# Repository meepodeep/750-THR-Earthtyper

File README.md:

# 750-THR-Earthtyper
The 1000-THR Earthmover shrunk down to a keyboard size!

# Why does this exist
I wanted to make an ultrakill themed keyboard, so i did!
# How to software
 1. DO BEFORE BUILD ITS EASIER I THINK
 2. Download QMK Toolbox and flash earthtyper via.hex onto the teensy by plugging it in, hitting the boot button and flashing. 
# How to build
1. solder the keyswitches onto the front of pcb using the laser cut Keyboard plate.svg , along with the teensy 2.0 and diodes on the back
2. Attach led strips to the inside of the case

4. Mask, engrave and cut the rear plate out of acrylic benjamin back.svg

5. Paint the engraved back plate
  
6. mount the keyboard pcb with m2 screws

7. cut the internal usb cable short on the mini b end

8. resolder the wire together so it doesnt have to coil and the usb c can still reach the outside
  
10. Use whatever method of securing the usb c cable to the pcb so that it aligns with the hole in the case

11. plug the mini b cable into the teensy.
 
12. mount the front peice with m3 screws while having the back plate on

#BOM
|Item                         |Price  |Quantity     |Use                       |Link                                                                                                                                                                                                                                                                                                                                                                                                                                                                                                                                                                                                                                      |
|-----------------------------|-------|-------------|--------------------------|------------------------------------------------------------------------------------------------------------------------------------------------------------------------------------------------------------------------------------------------------------------------------------------------------------------------------------------------------------------------------------------------------------------------------------------------------------------------------------------------------------------------------------------------------------------------------------------------------------------------------------------|
|KTT Kang White V3            |$24.89 |1x 90pcs     |Keyswitches               |https://www.aliexpress.us/item/3256807301426125.html?spm=a2g0o.detail.0.0.3d1b6S4E6S4EFs&mp=1&pdp_npi=5%40dis%21USD%21USD%2029.28%21USD%2024.89%21%21USD%2024.89%21%21%21%402101e83017622042732346918e6bca%2112000040979340369%21ct%21US%214381910819%21%211%210&gatewayAdapt=glo2usa                                                                                                                                                                                                                                                                                                                                                     |
|WS2812B 5v 2m 30 leds        |$5.16  |1x 2m 30 ip30|backlight                 |https://www.aliexpress.us/item/3256804103077154.html?spm=a2g0o.detail.0.0.58ecoyj9oyj91V&mp=1&pdp_npi=5%40dis%21USD%21USD%209.93%21USD%205.16%21%21USD%205.16%21%21%21%40210337c117622045728231910e80cb%2112000038338767353%21ct%21US%214381910819%21%211%210&gatewayAdapt=glo2usa                                                                                                                                                                                                                                                                                                                                                        |
|Teensy 2.0                   |$9.18  |1X           |mcu                       |https://www.aliexpress.us/item/3256803067426595.html?spm=a2g0o.tesla.0.0.4250OXmpOXmpuX&afTraceInfo=1005003253741347__pc__c_ppc_item_bridge_pc_main__xOYgwFH__1762223117433&gatewayAdapt=glo2usa4itemAdapt                                                                                                                                                                                                                                                                                                                                                                                                                                |
|usb adapter 20cm V8F-V3ST    |$2.24  |1x           |adapt the usb             |https://www.aliexpress.us/item/3256805661411472.html?spm=a2g0o.detail.0.0.79d0nuT8nuT8Ln&mp=1&pdp_npi=5%40dis%21USD%21USD%202.24%21USD%202.24%21%21USD%202.24%21%21%21%402101d97817622274198304062ed850%2112000034562878545%21ct%21US%214381910819%21%211%210&gatewayAdapt=glo2usa                                                                                                                                                                                                                                                                                                                                                        |
|transparent keycaps          |$18.82 |1x           |cap keys                  |https://www.aliexpress.us/item/3256809158263730.html?spm=a2g0o.detail.0.0.7867x8u0x8u0Bq&mp=1&pdp_npi=5%40dis%21USD%21USD%2020.05%21USD%2018.82%21%21USD%2018.82%21%21%21%40210337c117622048939932539e80cb%2112000048819835707%21ct%21US%214381910819%21%211%210&gatewayAdapt=glo2usa                                                                                                                                                                                                                                                                                                                                                     |
|1/8th in acrylic sheet       |$15    |1x           |be the backplate and plate|my makerspace!                                                                                                                                                                                                                                                                                                                                                                                                                                                                                                                                                                                                                            |
|m2 screws 4mm                |$2.24  |1x           |mount the pcb             |https://www.aliexpress.us/item/3256806812715286.html?spm=a2g0o.productlist.main.18.65975acdtLSuCT&algo_pvid=13e61948-fbdd-423b-8661-dafd5a1cd556&algo_exp_id=13e61948-fbdd-423b-8661-dafd5a1cd556-17&pdp_ext_f=%7B%22order%22%3A%22971%22%2C%22eval%22%3A%221%22%2C%22fromPage%22%3A%22search%22%7D&pdp_npi=6%40dis%21USD%213.11%212.75%21%21%213.11%212.75%21%402101f11417622055544167553ef72b%2112000038996754351%21sea%21US%214381910819%21X%211%210%21n_tag%3A-29919%3Bd%3A747bdf24%3Bm03_new_user%3A-29895&curPageLogUid=lCJAop0qt41n&utparam-url=scene%3Asearch%7Cquery_from%3A%7Cx_object_id%3A1005006999030038%7C_p_origin_prod%3A|
|m3 screws                    |$0     |gottem       |gottem                    |yo tengo                                                                                                                                                                                                                                                                                                                                                                                                                                                                                                                                                                                                                                  |
|pcbs                         |$33.74 |5x           |be a pcb                  |jlcpcb                                                                                                                                                                                                                                                                                                                                                                                                                                                                                                                                                                                                                                    |
|Diodes                       |$2.38  |2x           |be diodes                 |https://www.aliexpress.us/item/3256806058794623.html?spm=a2g0o.productlist.main.2.21c47164oKn0xm&algo_pvid=cf2a58fb-98bf-4c31-b0fb-3dd53bf9cf60&algo_exp_id=cf2a58fb-98bf-4c31-b0fb-3dd53bf9cf60-1&pdp_ext_f=%7B%22order%22%3A%22933%22%2C%22eval%22%3A%221%22%2C%22fromPage%22%3A%22search%22%7D&pdp_npi=6%40dis%21USD%211.72%211.19%21%21%2112.18%218.40%21%402101eede17622272036972994e35de%2112000036448323916%21sea%21US%214381910819%21X%211%210%21n_tag%3A-29919%3Bd%3A747bdf24%3Bm03_new_user%3A-29895&curPageLogUid=29HuQ5YR0viZ&utparam-url=scene%3Asearch%7Cquery_from%3A%7Cx_object_id%3A1005006245109375%7C_p_origin_prod%3A |
|Stablizers                   |$3.49  |             |stablize keys             |https://www.aliexpress.us/item/3256803076820380.html?spm=a2g0o.detail.0.0.44025Ziz5ZizBv&mp=1&pdp_npi=5%40dis%21USD%21USD%203.49%21USD%203.49%21%21USD%203.49%21%21%21%402101f54117624545764238043ec7b2%2112000024913121824%21ct%21US%214381910819%21%211%210&gatewayAdapt=glo2usa                                                                                                                                                                                                                                                                                                                                                        |
|Total without tax or shipping|$117.14|             |                          |                                                                                                                                                                                                                                                                                                                                                                                                                                                                                                                                                                                                                                          |
|Total                        |$121.32|             |                          |                                                                                                                                                                                                                                                                                                                                                                                                                                                                                                                                                                                                                                          |

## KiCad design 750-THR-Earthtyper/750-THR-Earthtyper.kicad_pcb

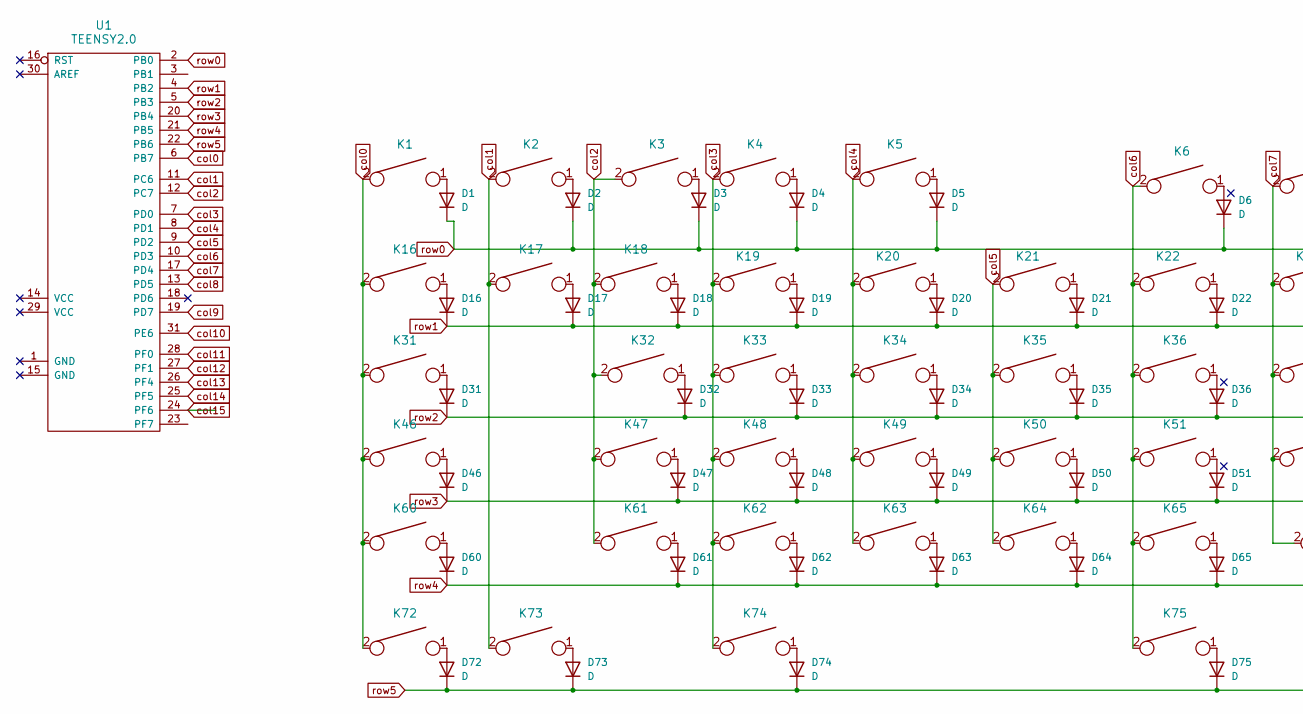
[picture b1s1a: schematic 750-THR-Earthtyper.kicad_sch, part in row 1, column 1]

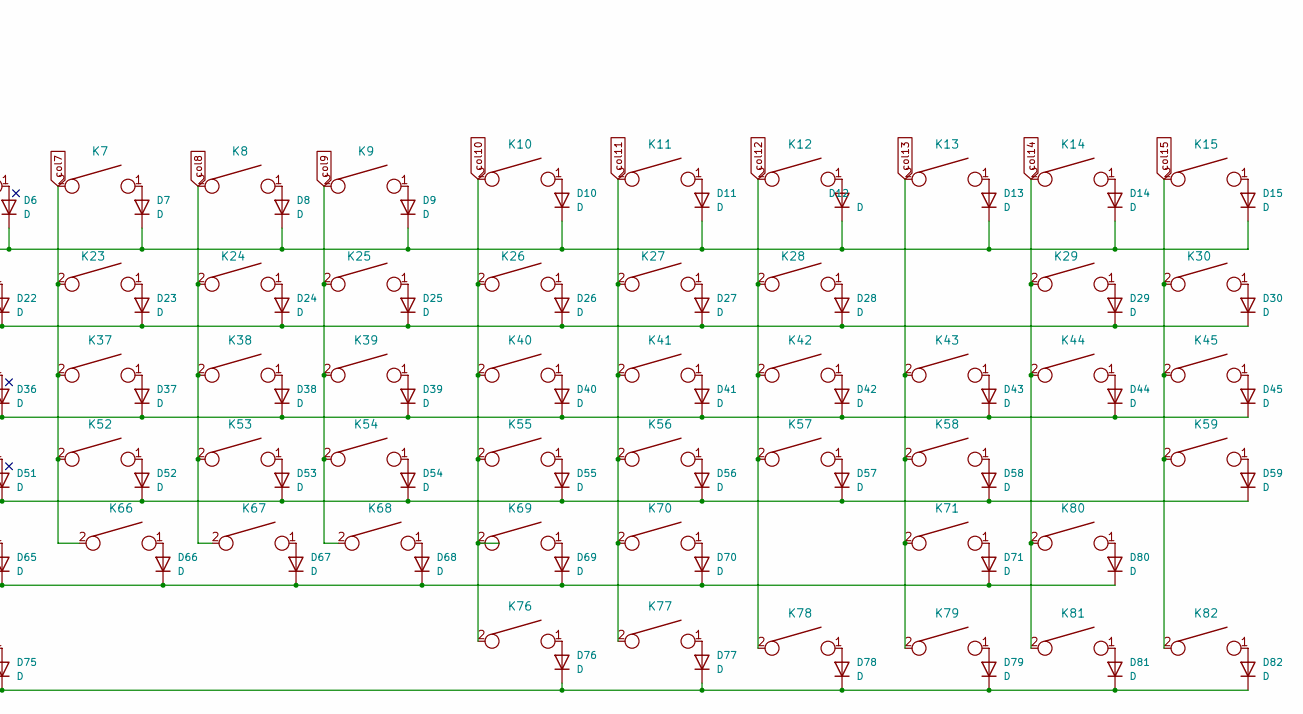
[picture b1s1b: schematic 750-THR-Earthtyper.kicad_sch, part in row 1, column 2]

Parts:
D1, D2, D3, D4, D5, D6, D7, D8, D9, D10, D11, D12, D13, D14, D15, D16, D17, D18, D19, D20, D21, D22, D23, D24, D25, D26, D27, D28, D29, D30, D31, D32, D33, D34, D35, D36, D37, D38, D39, D40, D41, D42, D43, D44, D45, D46, D47, D48, D49, D50, D51, D52, D53, D54, D55, D56, D57, D58, D59, D60, D61, D62, D63, D64, D65, D66, D67, D68, D69, D70, D71, D72, D73, D74, D75, D76, D77, D78, D79, D80, D81, D82: D; D_SOD123_axial
K1, K2, K3, K4, K5, K6, K7, K8, K9, K10, K11, K12, K13, K14, K15, K16, K17, K18, K19, K20, K21, K22, K23, K24, K25, K26, K27, K28, K30, K32, K33, K34, K35, K36, K37, K38, K39, K40, K41, K42, K43, K45, K47, K48, K49, K50, K51, K52, K53, K54, K55, K56, K57, K59, K61, K62, K63, K64, K65, K66, K67, K68, K69, K70, K71, K72, K73, K74, K75, K76, K77, K78, K79, K80, K81, K82: KEYSW; Mx_Alps_100
K29: KEYSW; Mx_Alps_200
K31, K44: KEYSW; Mx_Alps_150
K46: KEYSW; Mx_Alps_175
K58, K60: KEYSW; Mx_Alps_225
U1: TEENSY2.0; Teensy_20

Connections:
unnamed: D1.2 (A), K1.1
unnamed: D2.2 (A), K2.1
unnamed: D3.2 (A), K3.1
unnamed: D4.2 (A), K4.1
unnamed: D5.2 (A), K5.1
unnamed: D6.2 (A), K6.1
unnamed: D7.2 (A), K7.1
unnamed: D8.2 (A), K8.1
unnamed: D9.2 (A), K9.1
unnamed: D10.2 (A), K10.1
unnamed: D11.2 (A), K11.1
unnamed: D12.2 (A), K12.1
unnamed: D13.2 (A), K13.1
unnamed: D14.2 (A), K14.1
unnamed: D15.2 (A), K15.1
unnamed: D16.2 (A), K16.1
unnamed: D17.2 (A), K17.1
unnamed: D18.2 (A), K18.1
unnamed: D19.2 (A), K19.1
unnamed: D20.2 (A), K20.1
unnamed: D21.2 (A), K21.1
unnamed: D22.2 (A), K22.1
unnamed: D23.2 (A), K23.1
unnamed: D24.2 (A), K24.1
unnamed: D25.2 (A), K25.1
unnamed: D26.2 (A), K26.1
unnamed: D27.2 (A), K27.1
unnamed: D28.2 (A), K28.1
unnamed: D29.2 (A), K29.1
unnamed: D30.2 (A), K30.1
unnamed: D31.2 (A), K31.1
unnamed: D32.2 (A), K32.1
unnamed: D33.2 (A), K33.1
unnamed: D34.2 (A), K34.1
unnamed: D35.2 (A), K35.1
unnamed: D36.2 (A), K36.1
unnamed: D37.2 (A), K37.1
unnamed: D38.2 (A), K38.1
unnamed: D39.2 (A), K39.1
unnamed: D40.2 (A), K40.1
unnamed: D41.2 (A), K41.1
unnamed: D42.2 (A), K42.1
unnamed: D43.2 (A), K43.1
unnamed: D44.2 (A), K44.1
unnamed: D45.2 (A), K45.1
unnamed: D46.2 (A), K46.1
unnamed: D47.2 (A), K47.1
unnamed: D48.2 (A), K48.1
unnamed: D49.2 (A), K49.1
unnamed: D50.2 (A), K50.1
unnamed: D51.2 (A), K51.1
unnamed: D52.2 (A), K52.1
unnamed: D53.2 (A), K53.1
unnamed: D54.2 (A), K54.1
unnamed: D55.2 (A), K55.1
unnamed: D56.2 (A), K56.1
unnamed: D57.2 (A), K57.1
unnamed: D58.2 (A), K58.1
unnamed: D59.2 (A), K59.1
unnamed: D60.2 (A), K60.1
unnamed: D61.2 (A), K61.1
unnamed: D62.2 (A), K62.1
unnamed: D63.2 (A), K63.1
unnamed: D64.2 (A), K64.1
unnamed: D65.2 (A), K65.1
unnamed: D66.2 (A), K66.1
unnamed: D67.2 (A), K67.1
unnamed: D68.2 (A), K68.1
unnamed: D69.2 (A), K69.1
unnamed: D70.2 (A), K70.1
unnamed: D71.2 (A), K71.1
unnamed: D72.2 (A), K72.1
unnamed: D73.2 (A), K73.1
unnamed: D74.2 (A), K74.1
unnamed: D75.2 (A), K75.1
unnamed: D76.2 (A), K76.1
unnamed: D77.2 (A), K77.1
unnamed: D78.2 (A), K78.1
unnamed: D79.2 (A), K79.1
unnamed: D80.2 (A), K80.1
unnamed: D81.2 (A), K81.1
unnamed: D82.2 (A), K82.1
col0: K1.2, K16.2, K31.2, K46.2, K60.2, K72.2, U1.6 (PB7)
col1: K2.2, K17.2, K73.2, U1.11 (PC6)
col2: K3.2, K18.2, K32.2, K47.2, K61.2, U1.12 (PC7)
col3: K4.2, K19.2, K33.2, K48.2, K62.2, K74.2, U1.7 (PD0)
col4: K5.2, K20.2, K34.2, K49.2, K63.2, U1.8 (PD1)
col5: K21.2, K35.2, K50.2, K64.2, U1.9 (PD2)
col6: K6.2, K22.2, K36.2, K51.2, K65.2, K75.2, U1.10 (PD3)
col7: K7.2, K23.2, K37.2, K52.2, K66.2, U1.17 (PD4)
col8: K8.2, K24.2, K38.2, K53.2, K67.2, U1.13 (PD5)
col9: K9.2, K25.2, K39.2, K54.2, K68.2, U1.19 (PD7)
col10: K10.2, K26.2, K40.2, K55.2, K69.2, K76.2, U1.31 (PE6)
col11: K11.2, K27.2, K41.2, K56.2, K70.2, K77.2, U1.28 (PF0)
col12: K12.2, K28.2, K42.2, K57.2, K78.2, U1.27 (PF1)
col13: K13.2, K43.2, K58.2, K71.2, K79.2, U1.26 (PF4)
col14: K14.2, K29.2, K44.2, K80.2, K81.2, U1.25 (PF5)
col15: K15.2, K30.2, K45.2, K59.2, K82.2, U1.24 (PF6)
row0: D1.1 (K), D2.1 (K), D3.1 (K), D4.1 (K), D5.1 (K), D6.1 (K), D7.1 (K), D8.1 (K), D9.1 (K), D10.1 (K), D11.1 (K), D12.1 (K), D13.1 (K), D14.1 (K), D15.1 (K), U1.2 (PB0)
row1: D16.1 (K), D17.1 (K), D18.1 (K), D19.1 (K), D20.1 (K), D21.1 (K), D22.1 (K), D23.1 (K), D24.1 (K), D25.1 (K), D26.1 (K), D27.1 (K), D28.1 (K), D29.1 (K), D30.1 (K), U1.4 (PB2)
row2: D31.1 (K), D32.1 (K), D33.1 (K), D34.1 (K), D35.1 (K), D36.1 (K), D37.1 (K), D38.1 (K), D39.1 (K), D40.1 (K), D41.1 (K), D42.1 (K), D43.1 (K), D44.1 (K), D45.1 (K), U1.5 (PB3)
row3: D46.1 (K), D47.1 (K), D48.1 (K), D49.1 (K), D50.1 (K), D51.1 (K), D52.1 (K), D53.1 (K), D54.1 (K), D55.1 (K), D56.1 (K), D57.1 (K), D58.1 (K), D59.1 (K), U1.20 (PB4)
row4: D60.1 (K), D61.1 (K), D62.1 (K), D63.1 (K), D64.1 (K), D65.1 (K), D66.1 (K), D67.1 (K), D68.1 (K), D69.1 (K), D70.1 (K), D71.1 (K), D80.1 (K), U1.21 (PB5)
row5: D72.1 (K), D73.1 (K), D74.1 (K), D75.1 (K), D76.1 (K), D77.1 (K), D78.1 (K), D79.1 (K), D81.1 (K), D82.1 (K), U1.22 (PB6)

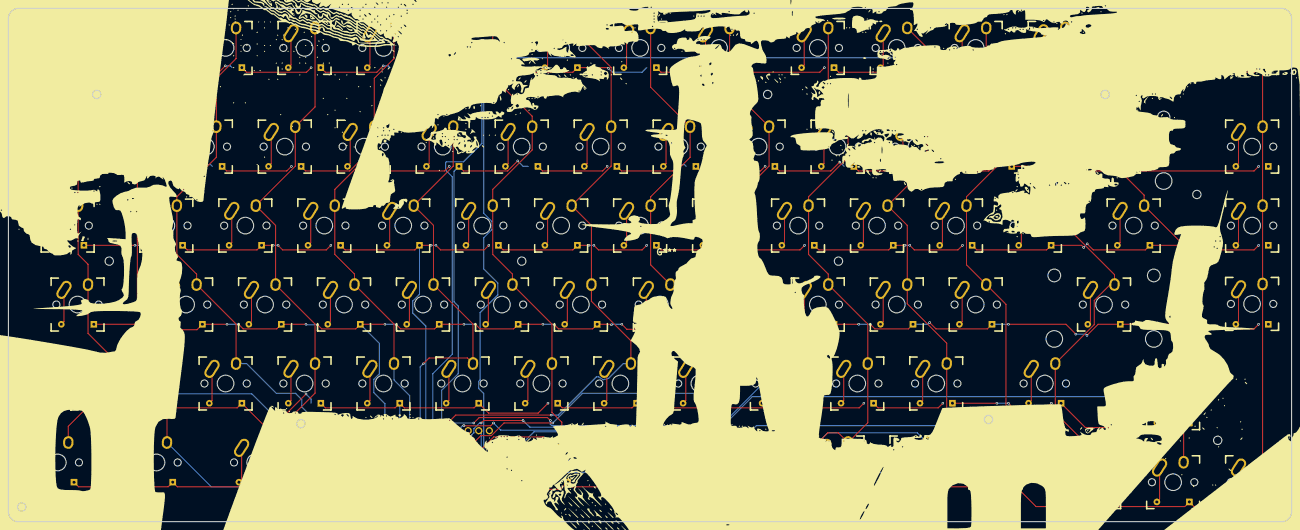
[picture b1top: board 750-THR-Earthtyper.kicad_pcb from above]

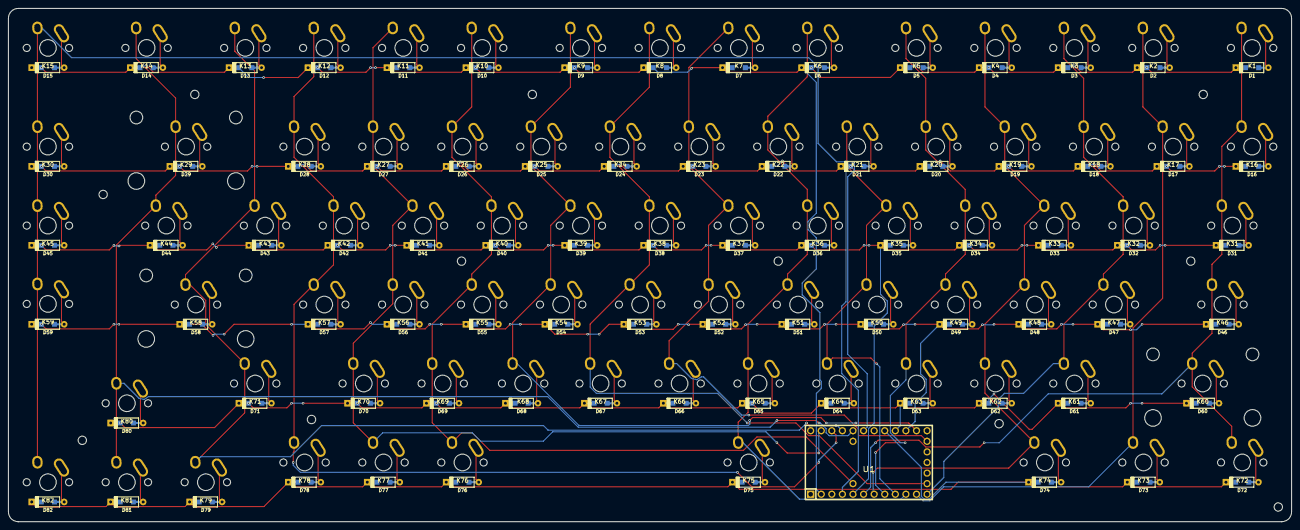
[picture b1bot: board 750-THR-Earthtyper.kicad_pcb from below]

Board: 2 copper layers, 307.9 x 123.2 mm, 165 parts (83 on the bottom side), 104 nets.

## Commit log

2025-11-02 started work
2025-11-03 added alot of things
2025-11-03 cleaned files
2025-11-03 chagned bom name
2025-11-03 wawa
2025-11-03 render
2025-11-05 updated the pcb to use net labels (thank you kai)
2025-11-06 fixed an error with the schematic and organized the schematic
2025-12-09 updated cad model
2026-01-15 finished keyboard plate hopefully it works this time
2026-01-31 Updated cad, FREE MEE
2026-01-31 AAGHG IM DONE
